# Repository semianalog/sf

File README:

Audio non-contact shortfinder

Still a prototype

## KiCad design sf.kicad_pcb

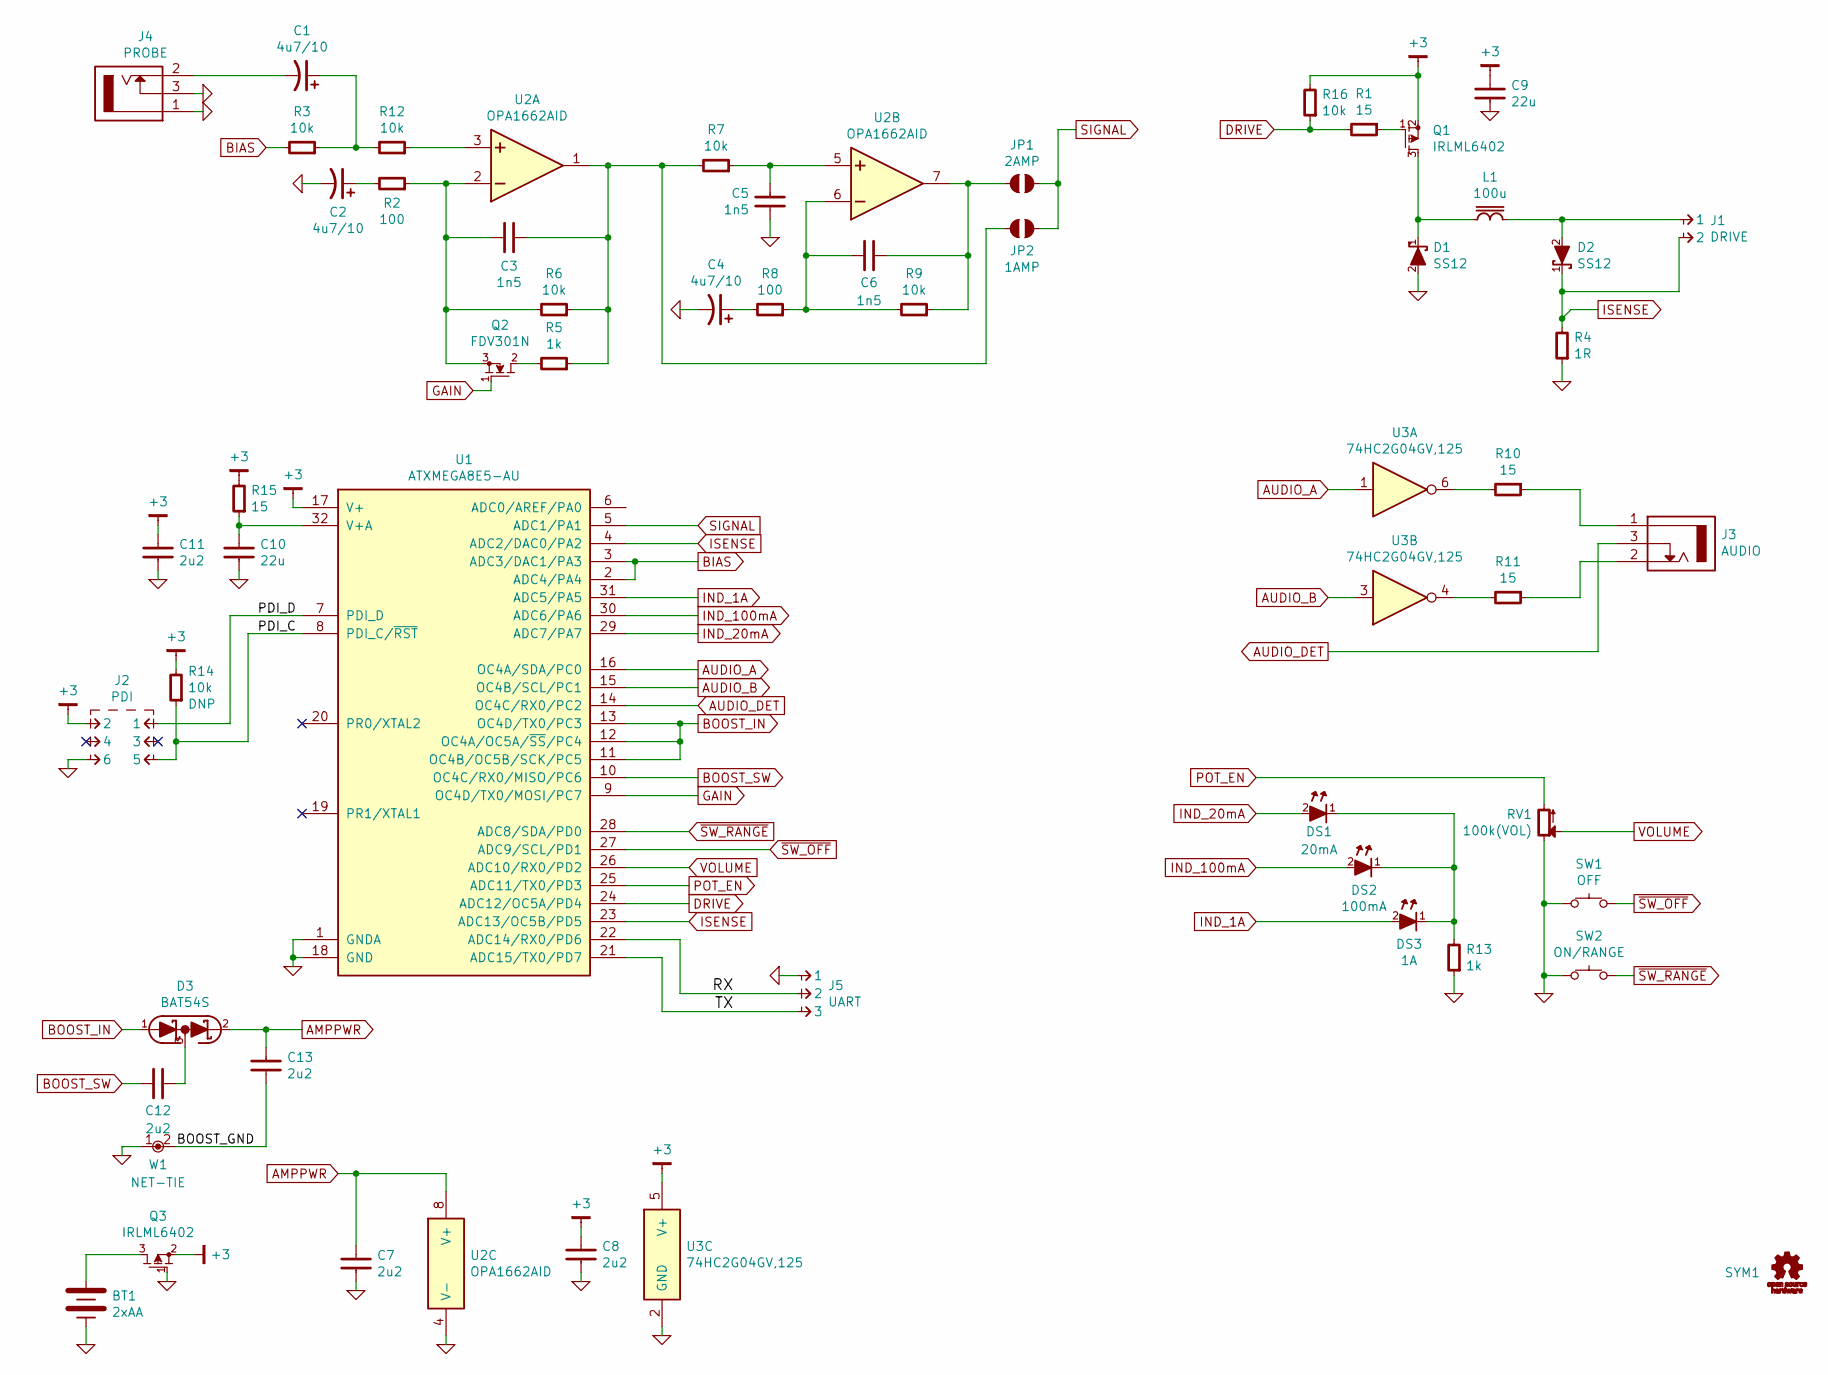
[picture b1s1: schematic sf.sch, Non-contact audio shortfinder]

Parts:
BT1: 2xAA
C1, C2, C4: 4u7/10; CAPMP2013X120; MPN F921A475MPA
C3, C5, C6: 1n5; CAPC2012X70
C7, C8, C11, C12, C13: 2u2; CAPC2012X70
C9, C10: 22u; CAPC3216X70
D1, D2: SS12; DIOM5326X292
D3: BAT54S; SOT-23
DS1: 20mA; LED-0603
DS2: 100mA; LED-0603
DS3: 1A; LED-0603
J1: DRIVE; CONN-100MIL-M-1x2
J2: PDI; CONN-100MIL-M-2x3
J3: AUDIO
J4: PROBE
J5: UART; CONN-100MIL-M-1x3
JP1: 2AMP; JUMPER-SOLDER-SMD
JP2: 1AMP; JUMPER-SOLDER-SMD
L1: 100u; BOURNS-RLB0914
Q1, Q3: IRLML6402; SOT-23
Q2: FDV301N; SOT-23
R1, R10, R11, R15: 15; RESC2012X50
R2, R8: 100; RESC2012X50
R3, R6, R7, R9, R12, R14, R16: 10k; RESC2012X50
R4: 1R; RESC3216X60
R5, R13: 1k; RESC2012X50
RV1: 100k(VOL); MPN 3352T-1-104LF
SW1: OFF; TE-FSMSM
SW2: ON/RANGE; TE-FSMSM
SYM1: OSHW-SCHEM-PCB6mm; OSHW-6mm
U1: ATXMEGA8E5-AU; QFP80P900X900X120-32; MPN ATXMEGA8E5-AU
U2: OPA1662AID; SOIC127P600X175-8; MPN OPA1662AID
U3: 74HC2G04GV,125; SOT-23-6; MPN 74HC2G04GV,125
W1: NET-TIE; NET-TIE-1mm

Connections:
+3: C8.1, C9.1, C11.1, J2.2, Q1.2 (S), Q3.2 (S), R14.2, R15.2, R16.2, U1.17 (V+), U3.5 (V+)
/BOOST_GND: C13.1, W1.2
/PDI_C: J2.5, R14.1, U1.8 (PDI_C/~RST)
/PDI_D: J2.1, U1.7 (PDI_D)
/RX: J5.2, U1.22 (ADC14/RX0/PD6)
/TX: J5.3, U1.21 (ADC15/TX0/PD7)
AMPPWR: C7.1, C13.2, D3.2 (K), U2.8 (V+)
AUDIO_A: U1.16 (OC4A/SDA/PC0), U3.1
AUDIO_B: U1.15 (OC4B/SCL/PC1), U3.3
AUDIO_DET: J3.3, U1.14 (OC4C/RX0/PC2)
BIAS: R3.2, U1.2 (ADC4/PA4), U1.3 (ADC3/DAC1/PA3)
BOOST_IN: D3.1 (A), U1.11 (OC4B/OC5B/SCK/PC5), U1.12 (OC4A/OC5A/~SS~/PC4), U1.13 (OC4D/TX0/PC3)
BOOST_SW: C12.2, U1.10 (OC4C/RX0/MISO/PC6)
DRIVE: R1.2, R16.1, U1.24 (ADC12/OC5A/PD4)
GAIN: Q2.1 (G), U1.9 (OC4D/TX0/MOSI/PC7)
GND: BT1.2 (-), C2.2, C4.2, C5.1, C7.2, C8.2, C9.2, C10.2, C11.2, D1.2 (A), J2.6, J4.1, J4.3, J5.1, Q3.1 (G), R4.1, R13.1, RV1.1, SW1.1, SW2.1, U1.1 (GNDA), U1.18 (GND), U2.4 (V-), U3.2 (GND), W1.1
IND_1A: DS3.2 (A), U1.31 (ADC5/PA5)
IND_20mA: DS1.2 (A), U1.29 (ADC7/PA7)
IND_100mA: DS2.2 (A), U1.30 (ADC6/PA6)
ISENSE: D2.1 (K), J1.2, R4.2, U1.4 (ADC2/DAC0/PA2), U1.23 (ADC13/OC5B/PD5)
unnamed: BT1.1 (+), Q3.3 (D)
unnamed: C1.1, R3.1, R12.2
unnamed: C1.2, J4.2
unnamed: C2.1, R2.2
unnamed: C3.1, JP2.1, R5.1, R6.1, R7.2, U2.1 (OUT)
unnamed: C3.2, Q2.3 (S), R2.1, R6.2, U2.2 (IN-)
unnamed: C4.1, R8.2
unnamed: C5.2, R7.1, U2.5 (IN+)
unnamed: C6.1, JP1.1, R9.1, U2.7 (OUT)
unnamed: C6.2, R8.1, R9.2, U2.6 (IN-)
unnamed: C10.1, R15.1, U1.32 (V+A)
unnamed: C12.1, D3.3 (COM)
unnamed: D1.1 (K), L1.2, Q1.3 (D)
unnamed: D2.2 (A), J1.1, L1.1
unnamed: DS1.1 (K), DS2.1 (K), DS3.1 (K), R13.2
unnamed: J3.1, R10.1
unnamed: J3.2, R11.1
unnamed: Q1.1 (G), R1.1
unnamed: Q2.2 (D), R5.2
unnamed: R10.2, U3.6
unnamed: R11.2, U3.4
unnamed: R12.1, U2.3 (IN+)
POT_EN: RV1.3, U1.25 (ADC11/TX0/PD3)
SIGNAL: JP1.2, JP2.2, U1.5 (ADC1/PA1)
VOLUME: RV1.2, U1.26 (ADC10/RX0/PD2)
~SW_OFF: SW1.2, U1.27 (ADC9/SCL/PD1)
~SW_RANGE: SW2.2, U1.28 (ADC8/SDA/PD0)

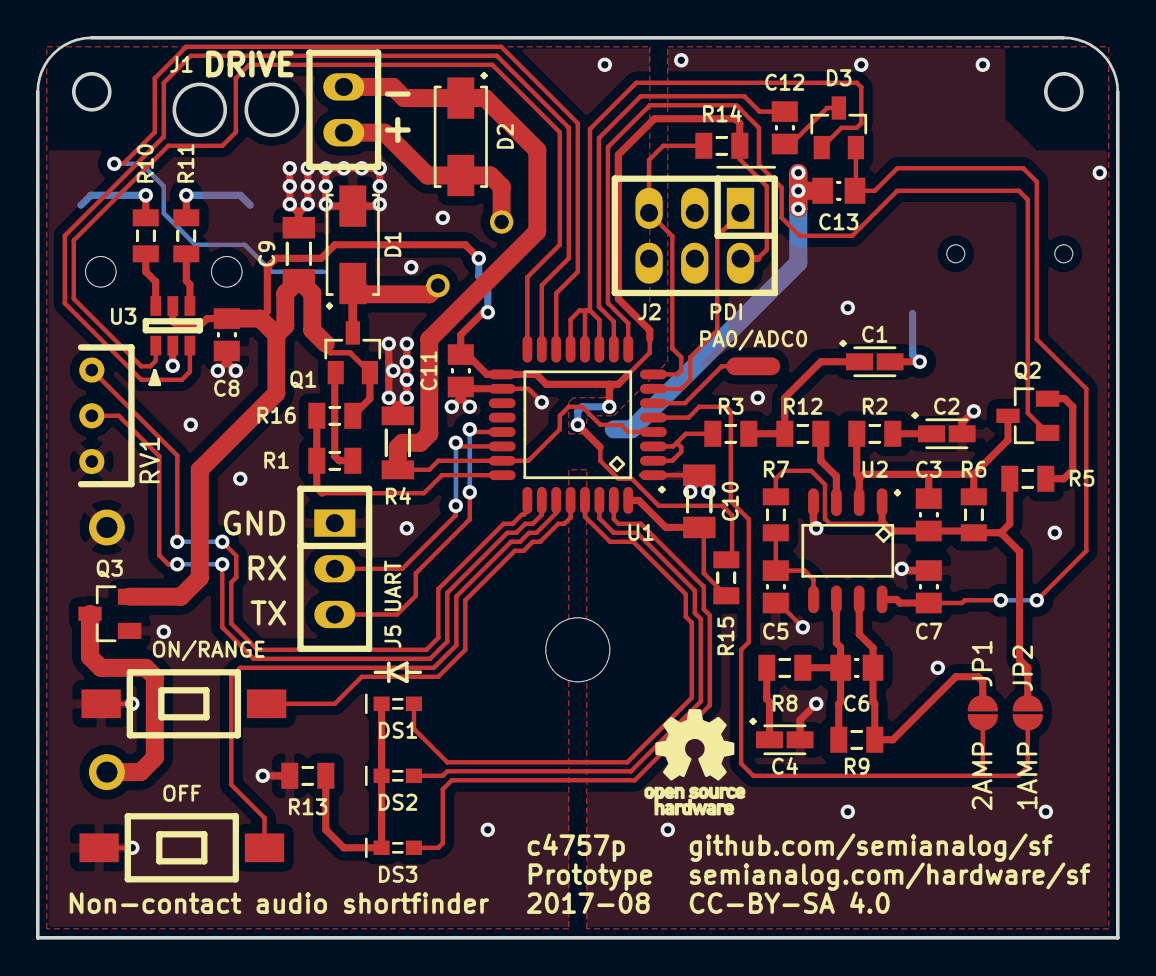
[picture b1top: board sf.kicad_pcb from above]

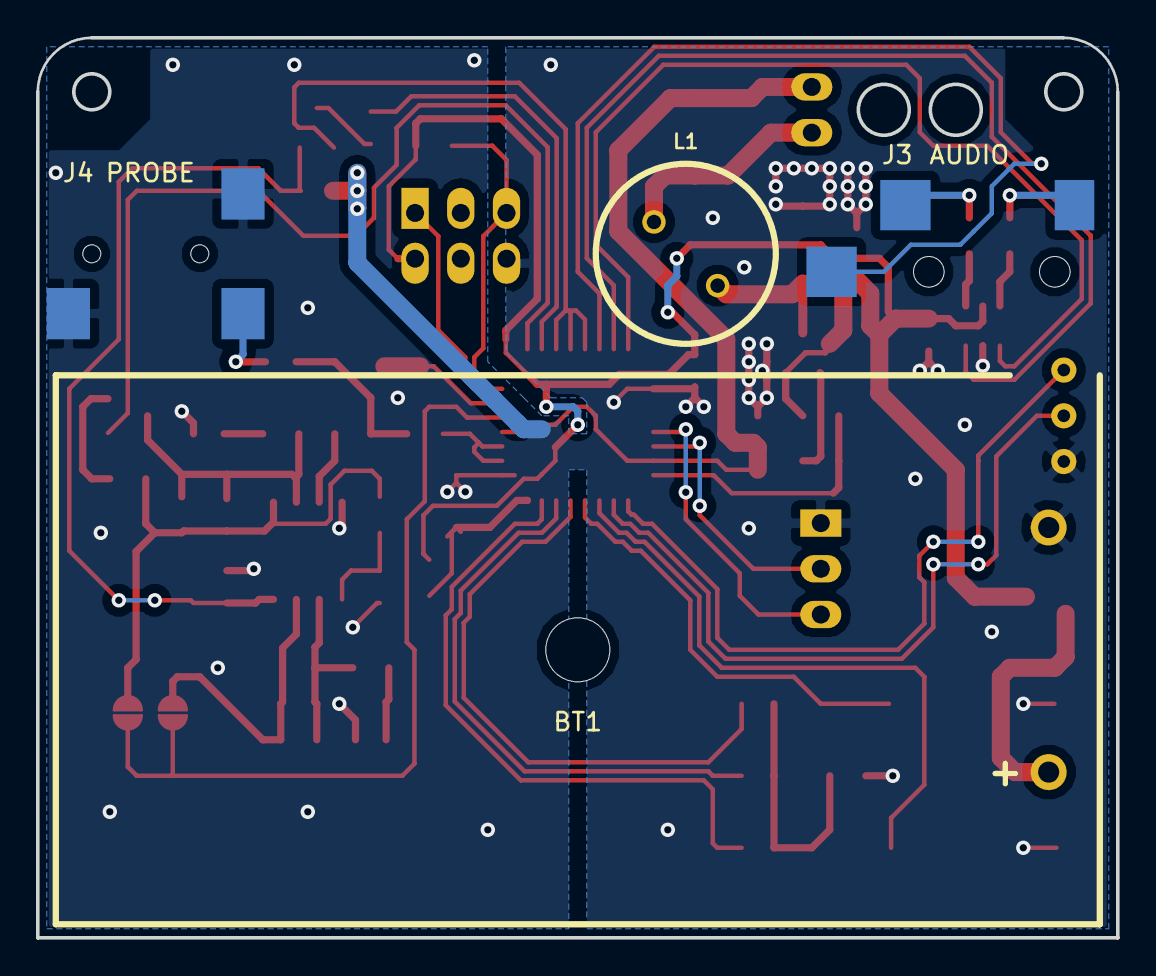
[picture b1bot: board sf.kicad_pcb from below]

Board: 2 copper layers, 60.0 x 50.0 mm, 55 parts (5 on the bottom side), 47 nets.

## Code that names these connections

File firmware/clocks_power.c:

#include "clocks_power.h"
#include "current_source.h"
#include "gpio.h"
#include <avr/io.h>
#include <avr/xmega.h>
#include <avr/sleep.h>
#include <avr/interrupt.h>

void start_fast_clock(void)
{
    const uint8_t en = OSC_RC32MEN_bm | OSC_RC32KEN_bm;
    const uint8_t rdy = OSC_RC32MRDY_bm | OSC_RC32KRDY_bm;

    OSC.CTRL |= en;
    while ((OSC.STATUS & rdy) != rdy);

    OSC.DFLLCTRL = OSC_RC32MCREF_RC32K_gc;
    DFLLRC32M.CTRL = DFLL_ENABLE_bm;

    OSC.PLLCTRL = OSC_PLLSRC_RC32M_gc /* div 4 */ | 16;
    OSC.CTRL |= OSC_PLLEN_bm;

    while (!(OSC.STATUS & OSC_PLLRDY_bm));

    _PROTECTED_WRITE(CLK.PSCTRL, CLK_PSADIV_1_gc | CLK_PSBCDIV_2_2_gc);
    _PROTECTED_WRITE(CLK.CTRL, CLK_SCLKSEL_PLL_gc);
}

void set_charge_pump_dc(bool run)
{
    _Static_assert(BOOST_IN_1_PORT == BOOST_IN_2_PORT, "Boost input pins must be on same port");
    _Static_assert(BOOST_IN_1_PORT == BOOST_IN_3_PORT, "Boost input pins must be on same port");
    VPORT_t * const boost_vport = VPORT_FOR_PIN(BOOST_IN_1);
    uint8_t const boost_mask = (1 << BOOST_IN_1_PIN) | (1 << BOOST_IN_2_PIN) | (1 << BOOST_IN_3_PIN);

    if (run) {
        boost_vport->OUT |= boost_mask;
    } else {
        boost_vport->OUT &= ~boost_mask;
    }
}

void enter_sleep(void)
{
    // TODO: Bias amplifier down and disable DAC
    // TODO: Disable charge pump, audio output, FET drive
    stop_dac();
    stop_timers();
    set_charge_pump_dc(false);
    stop_current_source();

    // TODO: Power down amplifier, volume pot, all LEDs
    WRITE_PIN(POT_EN, 0);
    WRITE_PIN(IND_1A, 0);
    WRITE_PIN(IND_100mA, 0);
    WRITE_PIN(IND_20mA, 0);

    PR.PRGEN = PR_XCL_bm | PR_RTC_bm | PR_EVSYS_bm | PR_EDMA_bm;
    PR.PRPA = PR_DAC_bm | PR_ADC_bm | PR_AC_bm;
    PR.PRPC = PR_TWI_bm | PR_USART0_bm | PR_SPI_bm | PR_HIRES_bm | PR_TC5_bm | PR_TC4_bm;
    PR.PRPD = PR_TWI_bm | PR_USART0_bm | PR_SPI_bm | PR_HIRES_bm | PR_TC5_bm | PR_TC4_bm;

    // Enable the pin change interrupt on the ON switch
    PORT_FOR_PIN(SW_RANGE)->INTMASK = 1 << SW_RANGE_PIN;
    PORT_FOR_PIN(SW_RANGE)->INTCTRL = PORT_INTLVL_HI_gc;

    set_sleep_mode(SLEEP_SMODE_PDOWN_gc);
    sleep_enable();
    sleep_cpu();

    for (;;);
}

ISR(PORTD_INT_vect)
{
    _PROTECTED_WRITE(RST.CTRL, RST_SWRST_bm);
    for(;;);
}

void enter_run(void)
{
    PR.PRGEN = PR_XCL_bm | PR_RTC_bm;
    PR.PRPC = PR_TWI_bm | PR_USART0_bm | PR_SPI_bm;
    PR.PRPD = PR_TWI_bm | PR_SPI_bm | PR_HIRES_bm;

    start_dac();
}

void stop_timers(void)
{
    TCC5.CTRLE = 0;
    TCC5.CTRLA = 0;
    TCC4.CTRLE = 0;
    TCC4.CTRLA = 0;
    TCD5.CTRLE = 0;
    TCD5.CTRLA = 0;
}

void start_dac(void)
{
    DACA.CTRLB = DAC_CHSEL_SINGLE1_gc;
    DACA.CTRLC = DAC_REFSEL_AVCC_gc;
    DACA.CTRLA = DAC_CH1EN_bm | DAC_LPMODE_bm | DAC_ENABLE_bm;
    DACA.CH1DATA = 0x7ff;
}

void stop_dac(void)
{
    DACA.CTRLA = 0;
}

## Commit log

2017-08-20 Add hardware definitions header
2017-08-24 Change firmware license to MIT
2017-08-24 Add simple firmware skeleton
2017-08-24 Different GPIO implementation
2017-08-25 Emit size when building
2017-08-25 Clock startup
2017-08-25 Enable GPIO slew rate limit
2017-08-25 Remove unnecessary include
2017-08-25 Begin sleep mode
2017-08-26 Add analog definitions
2017-09-02 Some power management stuff
2017-09-03 Start timer
2017-09-03 Bring up DAC
2017-09-07 Configure "power on" button
2017-09-07 Divide Clk_CPU by 4 for lower power.
    Clk_PER4 is still 32MHz and is used for the hi-res PWM extension.
2017-09-08 Boot into power-off
2017-09-09 Add current source control
2017-09-09 Very early audio output
2017-09-09 Better audio output, still needs heavy refactor
2017-09-09 Audio output refactoring
2017-09-09 Initial assembly instructions
2017-09-09 bleh
2017-09-09 Early ADC bringup
2017-09-10 Higher resolution audio
2017-09-10 Add event system ADC trigger
2017-09-10 Use cutoff frequency from hwdefs
2017-09-10 Calibrate ADC
2017-09-10 Minor cleanup
2017-09-10 Add notes for rev B
    - Quieter inductor
    - ADC reference is VCC/1.6, account for that in volpot
    - Volume pot sucks
2017-09-10 Add sampling code
2017-09-14 Update assembly instructions and schematic notes
2017-09-24 test blah
2017-09-24 blahblahblah
2017-09-24 10878

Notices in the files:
sf.kicad_pcb:
CC-BY-SA 4.0
